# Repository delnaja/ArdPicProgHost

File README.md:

# ArdPicProgHost
## GUI for Pic Programmer

If you would search the internet you will find quite some DIY pic programmers. However, those designs often either require a true seriell or parallel port instead of an easily available USB port or are designed around a pre-programmed controller assuming access to a programmer.

A compelling alternative would be the use of an Arduino as in the ArdPicProg. Load the Arduino sketch, the host program and add a prototype shield with a very limited number of additional components to build your pic programmer. This programmer features also a ICD connector and an RJ-11 jack (ICD2) interface. The complete project including hard- and software is open source and is released under the GNU General Public License Version 3. You can build your own ArdPicProg by using the available kit or especially designed PCB.

The complete setup and the application of the ArdPicProg is described in more detail on https://makerprojekte.de/en/arduino-pic-programmer/. This page also features a comprehensive User's Guide.

One element of the ArdPicProg - tool chain is a host software. You can select between two options: the terminal program "PicProgTerm" or the "ArdPicProgHost" application for Windows with a graphical user interface. The source code for both programs can be found in respective repositories on github/makerprojects.

Changes: 
24.05.2021: PIC16F627A, PIC16F628A and PIC16F648A support added

14.10.2021: PIC12F629, PIC12F675 support added – 5V PIC_VDD power supply via D2 arduino pin. OSCCAL is overwritten

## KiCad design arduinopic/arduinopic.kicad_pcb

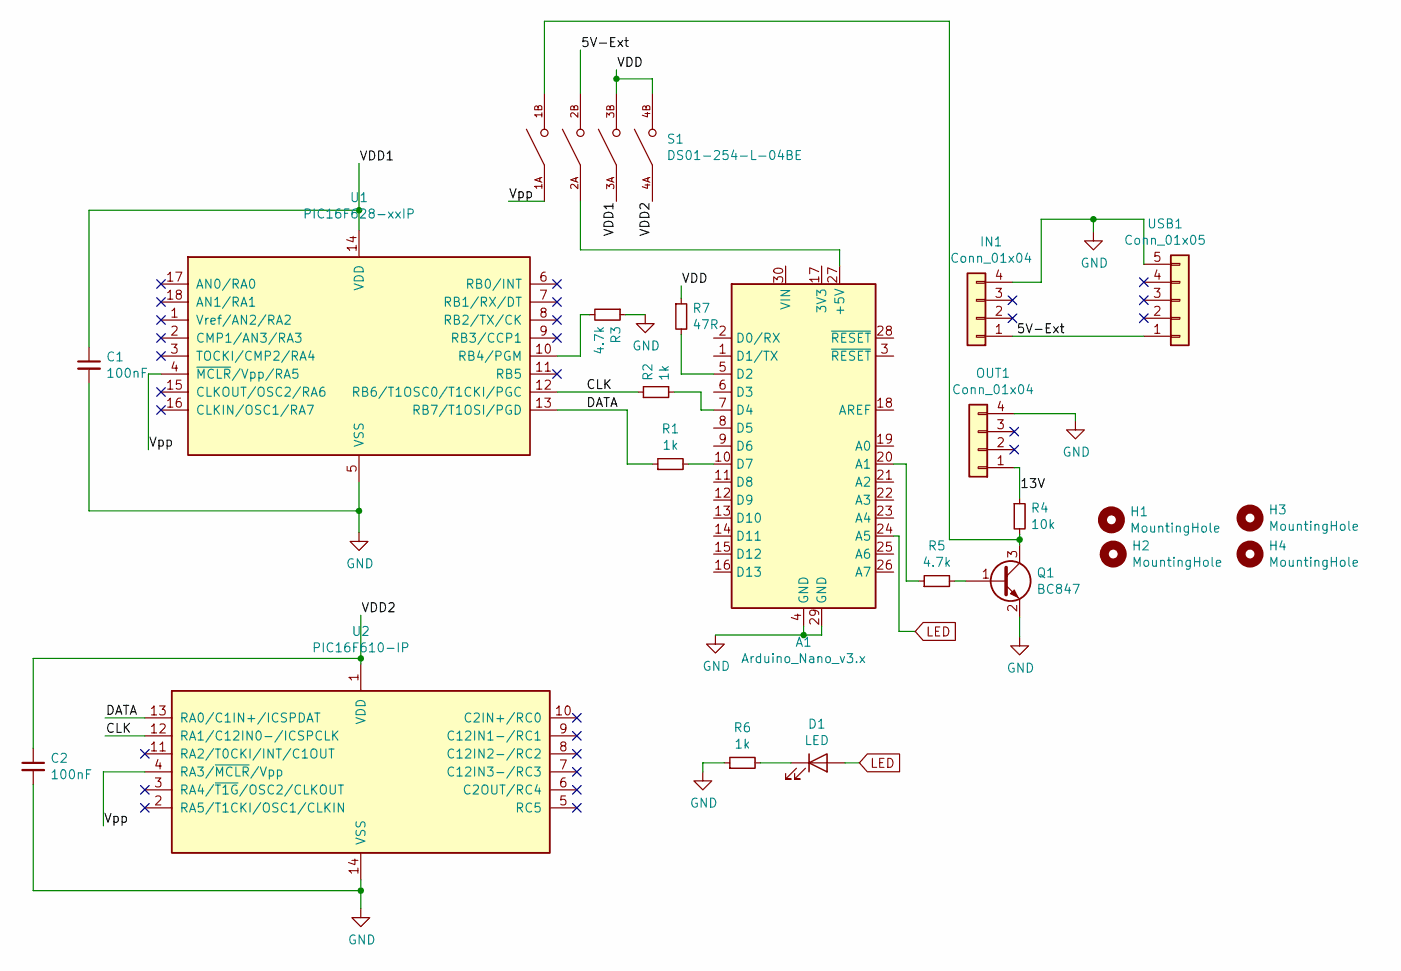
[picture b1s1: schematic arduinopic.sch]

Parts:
A1: Arduino_Nano_v3.x; Arduino_Nano
C1, C2: 100nF; C_1206_3216Metric_Pad1.42x1.75mm_HandSolder
D1: LED; LED_1206_3216Metric_Pad1.42x1.75mm_HandSolder
H1, H2, H3, H4: MountingHole; MountingHole_2.2mm_M2_Pad
IN1: Conn_01x04; PinSocket_1x04_P2.54mm_Vertical
OUT1: Conn_01x04; PinSocket_1x04_P2.54mm_Vertical
Q1: BC847; SOT-23_Handsoldering
R1, R2, R6: 1k; R_1206_3216Metric_Pad1.42x1.75mm_HandSolder
R3, R5: 4.7k; R_1206_3216Metric_Pad1.42x1.75mm_HandSolder
R4: 10k; R_1206_3216Metric_Pad1.42x1.75mm_HandSolder
R7: 47R; R_1206_3216Metric_Pad1.42x1.75mm_HandSolder
S1: DS01-254-L-04BE; SW_DS01-254-L-04BE; PARTREV 1.0
U1: PIC16F628-xxIP; DIP-18_W7.62mm_Socket_LongPads
U2: PIC16F610-IP; DIP-14_W7.62mm_Socket_LongPads
USB1: Conn_01x05; PinHeader_1x05_P2.54mm_Vertical

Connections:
/5V-Ext: IN1.1, S1.2B, USB1.1
/13V: OUT1.1, R4.1
/CLK: R2.1, U1.12 (RB6/T1OSC0/T1CKI/PGC), U2.12 (RA1/C12IN0-/ICSPCLK)
/DATA: R1.1, U1.13 (RB7/T1OSI/PGD), U2.13 (RA0/C1IN+/ICSPDAT)
/VDD: R7.1, S1.3B, S1.4B
/VDD1: C1.1, S1.3A, U1.14 (VDD)
/VDD2: C2.1, S1.4A, U2.1 (VDD)
/Vpp: S1.1A, U1.4 (~MCLR~/Vpp/RA5), U2.4 (RA3/~MCLR~/Vpp)
GND: A1.4 (GND), A1.29 (GND), C1.2, C2.2, IN1.4, OUT1.4, Q1.2 (E), R3.1, R6.1, U1.5 (VSS), U2.14 (VSS), USB1.5
LED: A1.24 (A5), D1.2 (A)
unnamed: A1.5 (D2), R7.2
unnamed: A1.7 (D4), R2.2
unnamed: A1.10 (D7), R1.2
unnamed: A1.20 (A1), R5.1
unnamed: A1.27 (+5V), S1.2A
unnamed: D1.1 (K), R6.2
unnamed: Q1.1 (B), R5.2
unnamed: Q1.3 (C), R4.2, S1.1B
unnamed: R3.2, U1.10 (RB4/PGM)

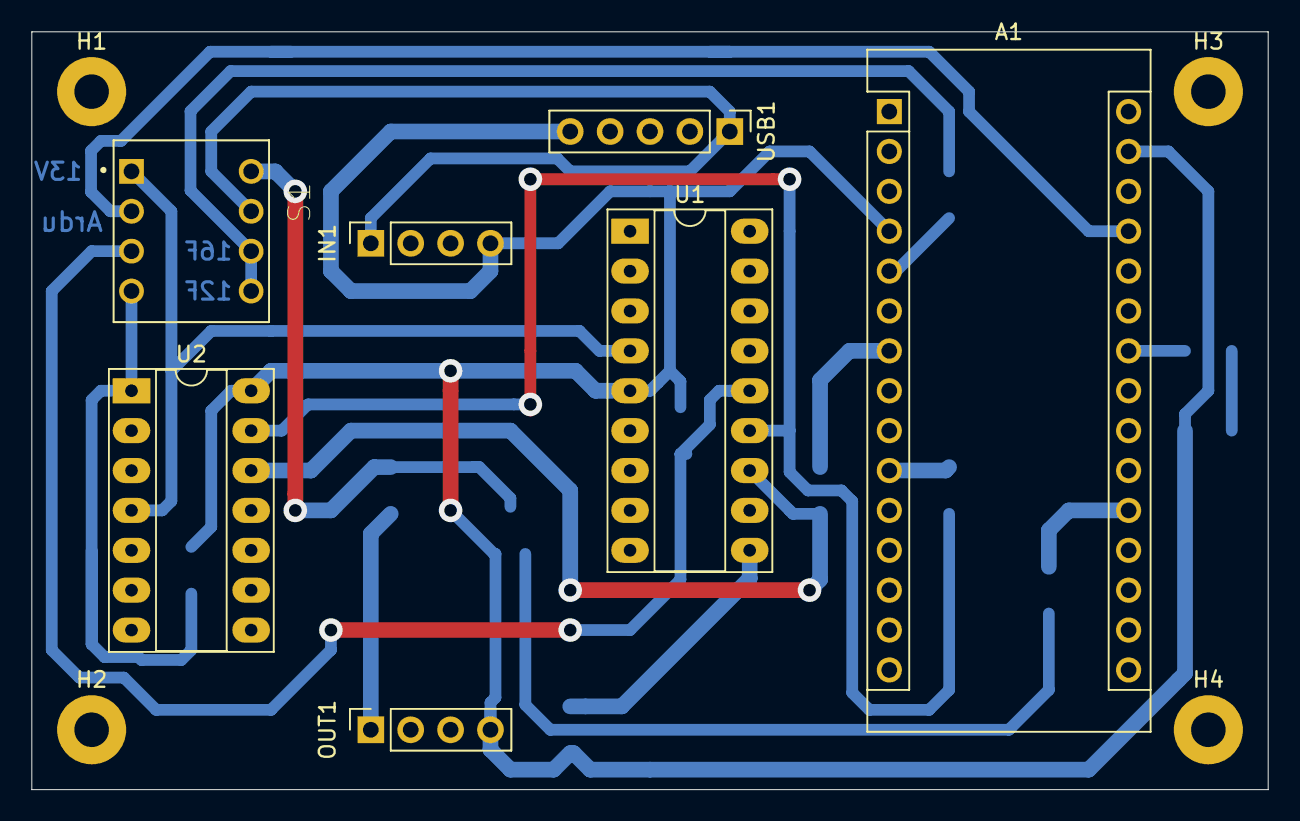
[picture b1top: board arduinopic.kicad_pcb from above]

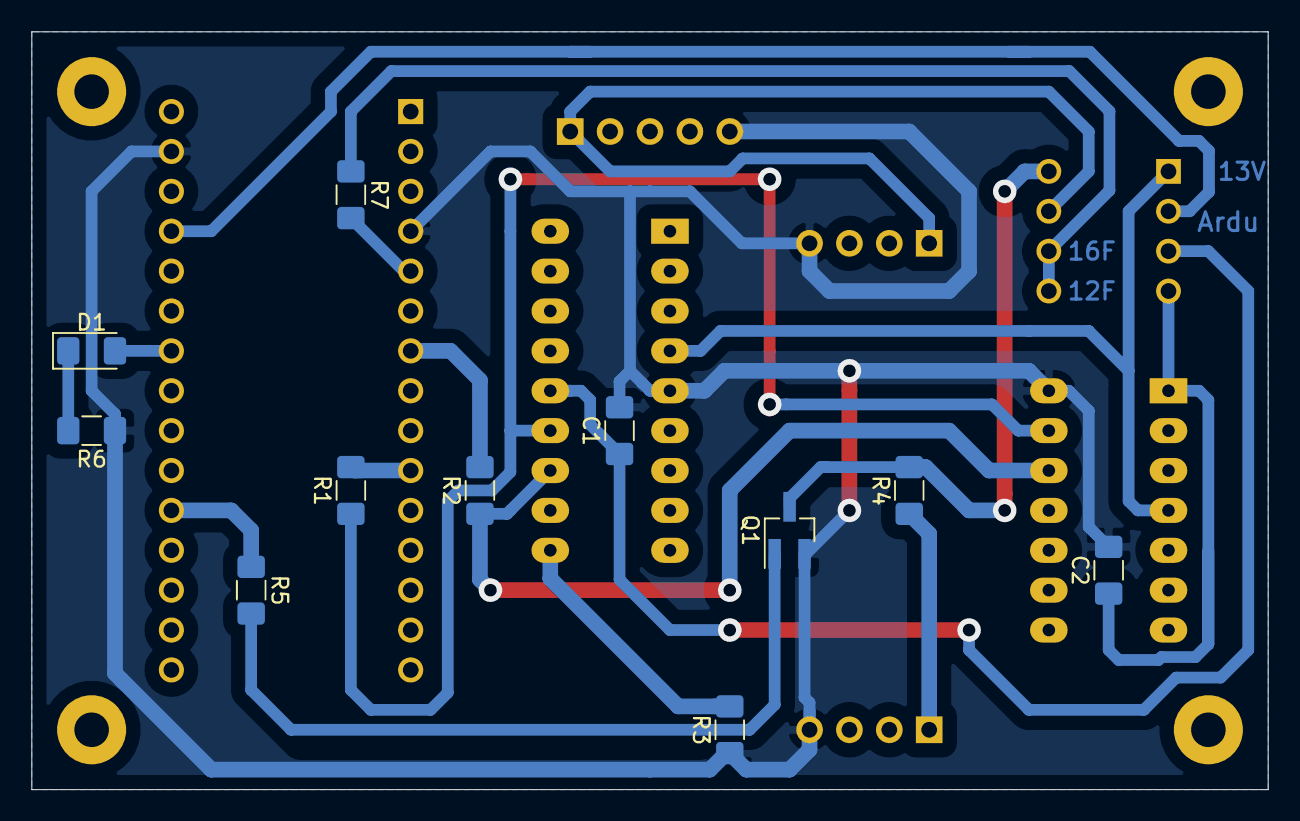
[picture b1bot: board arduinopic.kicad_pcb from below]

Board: 2 copper layers, 78.7 x 48.3 mm, 22 parts (11 on the bottom side), 19 nets.

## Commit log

2021-05-24 PIC16F627A, PIC16F628A and PIC16F648A support added
2021-09-10 Server side for arduino and kicad realization added
2021-10-14 PIC12F629, PIC12F675 support added
2021-10-14 FlashType and Flash visibility for PIC12F fixed, ArdPicProgHost.exe updated
